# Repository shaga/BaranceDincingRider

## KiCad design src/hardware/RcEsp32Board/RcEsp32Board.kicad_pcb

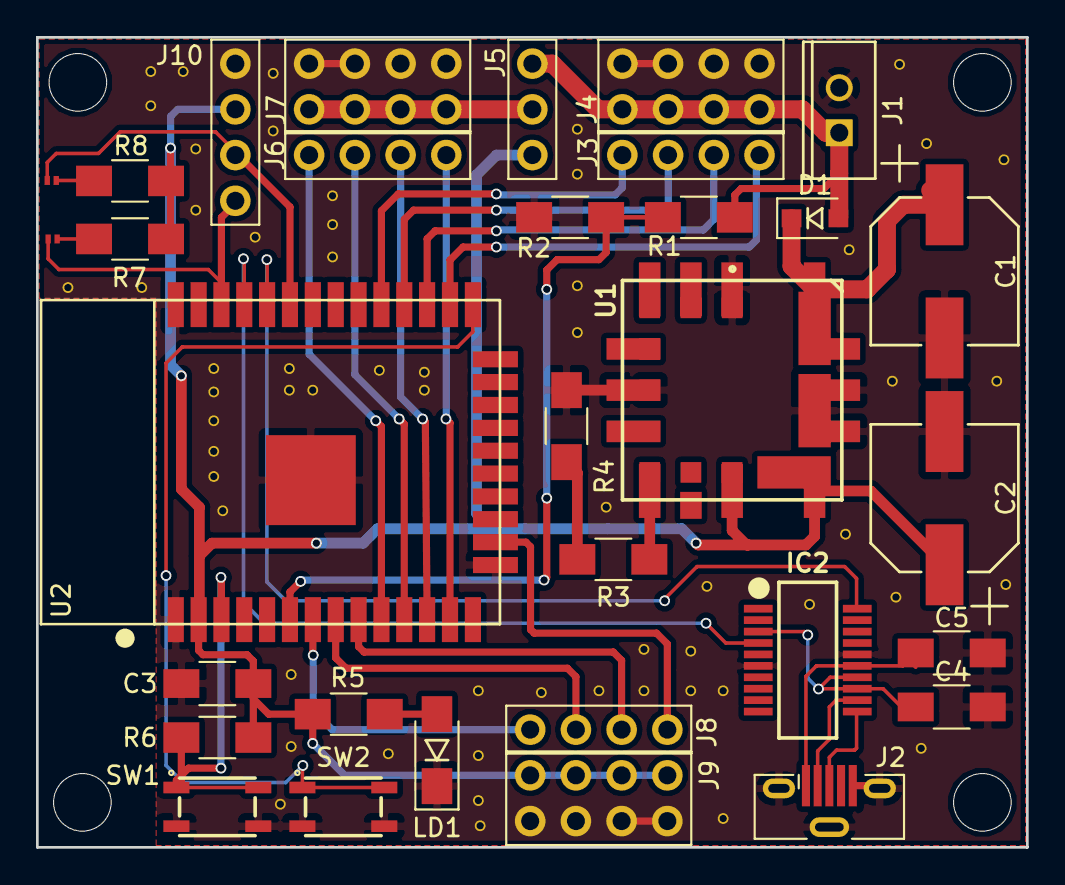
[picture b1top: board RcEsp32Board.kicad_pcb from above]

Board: 2 copper layers, 55.0 x 45.0 mm, 32 parts (0 on the bottom side), 33 nets.

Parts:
C1, C2: CP; elecon_8x10_5
C3, C4, C5: 0.1u; C_1206_HandSoldering
D1: D; D_SOD-323_HandSoldering
IC2: FT231XS-R; SOP64P599X175-20N
J1: Conn_01x02; EH-2P
J2: USB_B_Micro; USB_Micro-B_Molex-105133-0001
J3, J6, J8, J10: Conn_01x04; PinHeader01x04
J4, J7, J9: Conn_02x04_Odd_Even; PinHeader02x04
J5: Conn_01x03; PinHeader01x03
LD1: LED; LED_1206_HandSoldering
P1, P2: PAD
R1: 20K; R_1206_HandSoldering
R2, R6: 10K; R_1206_HandSoldering
R3: 1.5K; R_1206_HandSoldering
R4: 680; R_1206_HandSoldering
R5: 150; R_1206_HandSoldering
R7, R8: R; R_1206_HandSoldering
SW1, SW2: SKRPACE010; SMT(4.2X3.2)
U1: OKL-T_3-W12N-C; OKL-T3-W12
U2: ESP-WROOM-32

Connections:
+3V3: C2.1, C3.1, J5.3, J9.1, J9.3, J9.5, J9.7, J10.2, R5.2, R6.1, R7.1, R8.1, U1.4, U1.5, U2.2
+BATT: D1.2, J1.1, J4.1, J4.3, J4.5, J4.7, J5.1, R1.2
/BATT_CHECK: R1.1, R2.1, U2.6
/INPUT0: J8.1, U2.7
/INPUT1: J8.2, U2.8
/INPUT2: J8.3, U2.9
/INPUT3: J8.4, U2.16
/IO0: J6.1, U2.10
/IO1: J6.2, U2.11
/IO2: J6.3, U2.12
/IO3: J6.4, U2.13
/PROGRAM: SW2.1, SW2.2, U2.25
/RESET: R6.2, SW1.1, SW1.2, U2.3
/RXD: IC2.20, U2.34
/SCL: J10.4, P1.2, U2.36
/SDA: J10.3, P2.2, U2.33
/SVR0: J3.1, U2.29
/SVR1: J3.2, U2.28
/SVR2: J3.3, U2.27
/SVR3: J3.4, U2.26
/TXD: IC2.4, U2.35
GND: C1.2, C2.2, C3.2, C4.2, C5.2, IC2.6, IC2.16, J1.2, J2.5, J2.6, J4.2, J4.4, J4.6, J4.8, J7.2, J7.4, J7.6, J7.8, J9.2, J9.4, J9.6, J9.8, J10.1, LD1.1, R2.2, R4.2, SW1.3, SW1.4, SW2.3, SW2.4, U1.1, U1.3, U1.7, U2.1, U2.15, U2.38, U2.39
unnamed: C1.1, D1.1, U1.2
unnamed: C4.1, IC2.3, IC2.13, IC2.14
unnamed: C5.1, IC2.15, J2.1
unnamed: IC2.11, J2.3
unnamed: IC2.12, J2.2
unnamed: J5.2, J7.1, J7.3, J7.5, J7.7
unnamed: LD1.2, R5.1
unnamed: P1.1, R7.2
unnamed: P2.1, R8.2
unnamed: R3.1, U1.6
unnamed: R3.2, R4.1

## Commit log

2018-12-28 update gitignore
2018-12-28 start design board
2018-12-30 add components and update sch
2019-01-06 update sch/pcb, add gerber data.
2019-08-03 add sch pdf
2019-08-03 add firm/board jigu
